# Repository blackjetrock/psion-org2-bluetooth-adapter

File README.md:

# psion-org2-bluetooth-adapter
Bluetooth adapter for Psion Organiser II

NOTE:Very much a prototype that needs modifications to run properly.

An adapter for the Psion Organiser II which has the Comms Link ROM in a Pico. hardware for bluetooth is a WROOM module.
The unit plugs in to the top slot of a PSion Organiser II and allows Bluetooth traffic to be passed on to the organiser.
The original comms link code runs on the Pico as it emulates a datapack ROM.

V1.0
----

Prototype PCB that is not designed to fit in a case.
Power from 1 cell Li-ion. Regulator should take input from jack and drop it to 5V. Battery charger/power path outputs 5.5V down to battery voltage. 
Pico takes output from regulator (5.5V to VBAT) and buck boosts to 3V3. 3V3 output from Pico drives external circuitry up to 300mA.
If running WROOM off 3V3 is too much then use 3V3 regulator off VREG.

V1.1
----

Movd charging circuit to the ETA6002 as soldering the BQxxx was tricky. This circuit doesn't really work as the datasheet has little data so I'm not sure about a lot of aspects of this chip. The code has had to be rewritten to not use interrupts. Instead of using one of the hardware UARTs and a PIO UART the code now uses two UARTS made fom PIOs. This doesn't use interrupts and works a lot better.
Master mode works on th elatest code and I have had two organisers communicating, on ein master mode and pone in slave using the TERM menu. Seems OK. The TRANSMIT menu option messes something up though, although it looks like the data is sent.
Turn off handshaking in the SETUP menu.
9600,n,8,1 is the Psion setting that is needed.

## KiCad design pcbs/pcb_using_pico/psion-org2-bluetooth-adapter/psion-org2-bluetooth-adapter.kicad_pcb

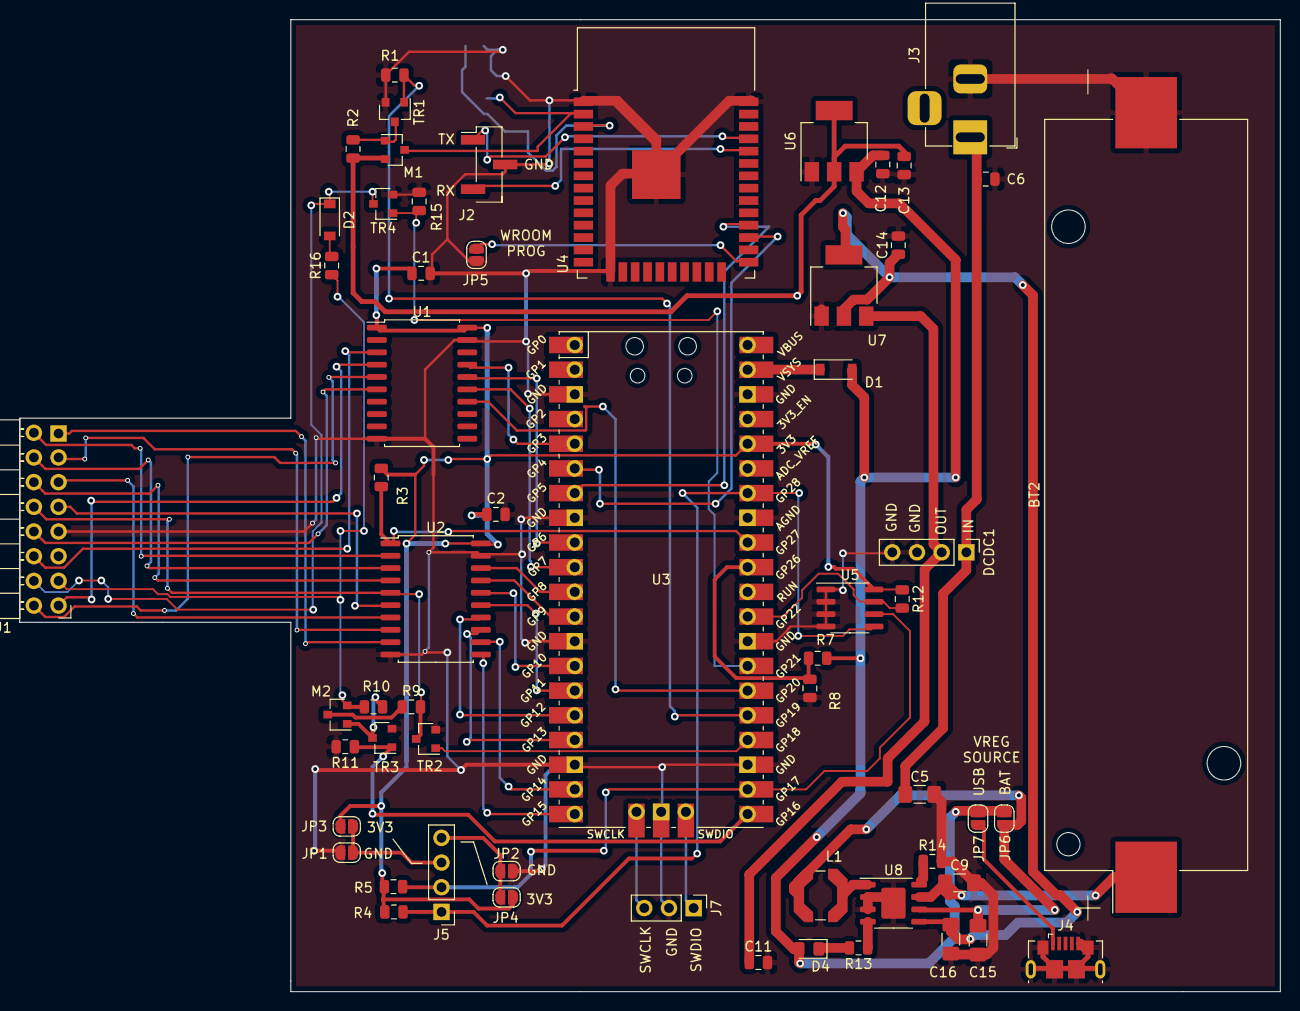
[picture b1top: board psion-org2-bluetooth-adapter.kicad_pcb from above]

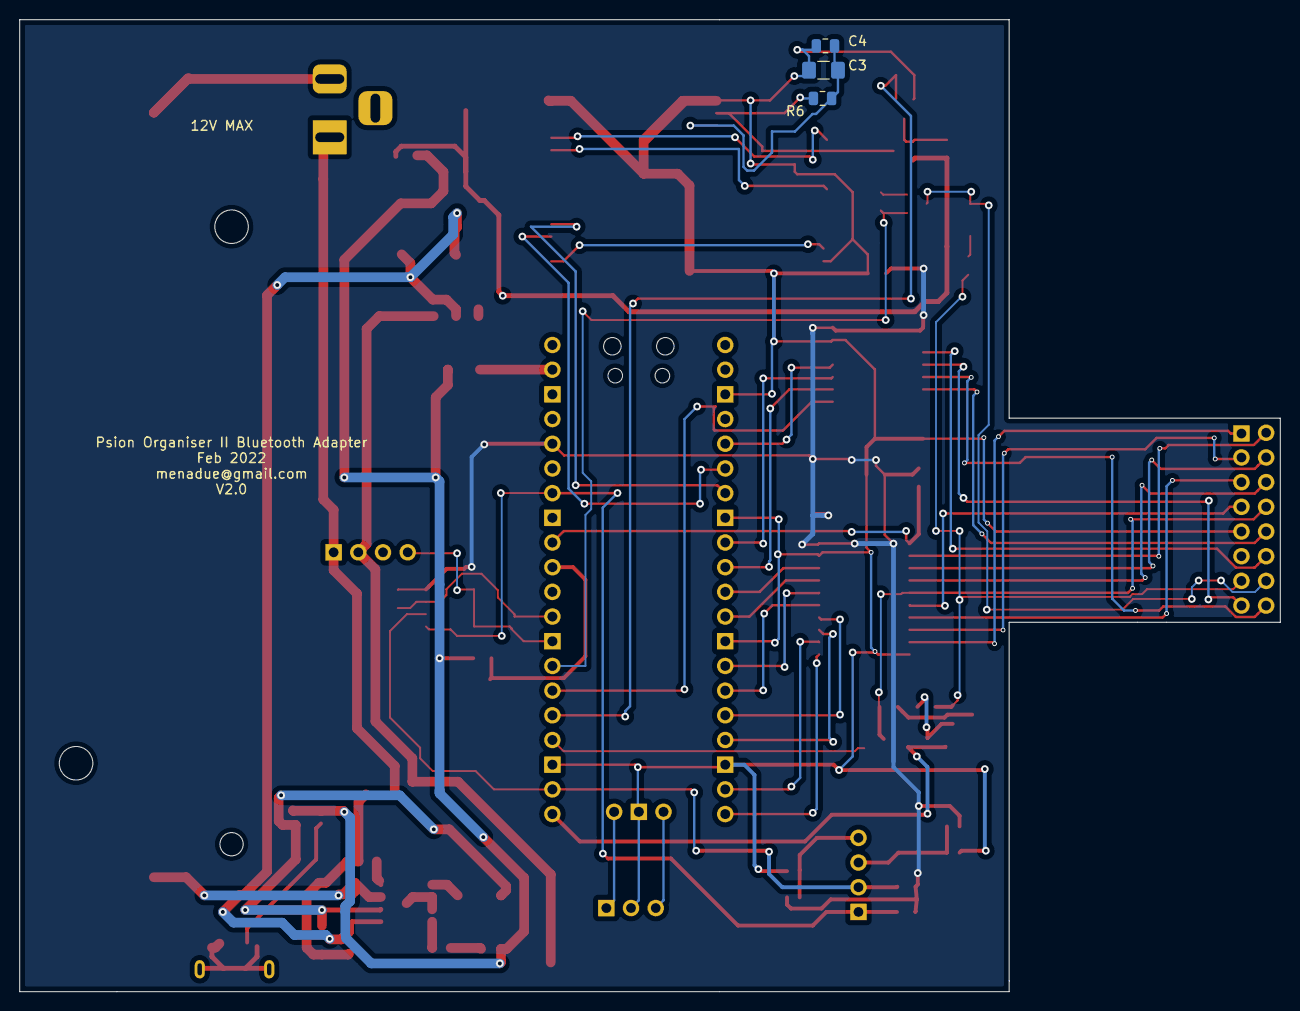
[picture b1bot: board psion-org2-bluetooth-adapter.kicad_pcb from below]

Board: 2 copper layers, 129.7 x 100.0 mm, 62 parts (3 on the bottom side), 65 nets.

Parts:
BT2: Battery_Cell; BatteryHolder_Keystone_1042_1x18650
C1, C2, C4, C6, C11, C12, C13, C14: 100nF; C_0805_2012Metric
C3: 4u7; C_1206_3216Metric_Pad1.42x1.75mm_HandSolder
C5, C16: 10uF; C_1206_3216Metric_Pad1.42x1.75mm_HandSolder
C9: 1uF; C_1206_3216Metric_Pad1.42x1.75mm_HandSolder
C15: 22uF; C_1206_3216Metric_Pad1.42x1.75mm_HandSolder
D1, D2: D_Schottky; D_SOD-123
D4: LED; LED_0805_2012Metric_Pad1.15x1.40mm_HandSolder
DCDC1: dcdc; PinHeader_1x04_P2.54mm_Vertical
J1: Conn_02x08_Odd_Even; Psion_datapak_2x08_P2.54mm_Horizontal
J2: Conn_01x03_Female; PinHeader_1x03_P2.54mm_Vertical_SMD_Pin1Left
J3: Barrel_Jack; BarrelJack_Horizontal
J4: Connector_USB_B_Micro; USB_Micro-B_GCT_USB3076-30-A
J5: Conn_01x04_Female; PinHeader_1x04_P2.54mm_Vertical
J7: Conn_01x03_Female; PinHeader_1x03_P2.54mm_Vertical
JP1, JP2, JP3, JP4, JP5, JP6, JP7: Jumper_NO_Small; SolderJumper-2_P1.3mm_Open_RoundedPad1.0x1.5mm
L1: 2.2uH; L_Coilcraft_LPS5030
M1: P-CHANNEL-MOSFET; SOT-23
M2: Si2301; SOT-23
R1, R2, R3, R6, R7, R8, R9, R12: R_Small; R_0805_2012Metric
R4, R5: 4k7; R_0805_2012Metric
R10, R11: 10k; R_0805_2012Metric
R13: 2k2; R_0805_2012Metric
R14: 500R; R_0805_2012Metric
R15, R16: 47k; R_0805_2012Metric
TR1, TR4: New_Library_Si2302CDS-n-channel; SOT-23
TR2: si2302; SOT-23
TR3: Si2302; SOT-23
U1, U2: 74LS245; SOIC-20W_7.5x12.8mm_P1.27mm
U3: Pico; RPi_Pico_SMD_TH
U4: ESP32-WROOM-32
U5: 24LC32; SOIC-8_3.9x4.9mm_P1.27mm
U6: AMS1117-3.3; SOT-223-3_TabPin2
U7: AMS1117-5.0; SOT-223-3_TabPin2
U8: ETA6002; SOIC-8-1EP_3.9x4.9mm_P1.27mm_EP2.514x3.2mm

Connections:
+3V3: C1.1, C2.1, JP3.2, JP4.2, R3.1, R4.1, R5.1, R12.1, U1.1, U1.20, U2.20, U3.36, U5.8
AC: D2.1, J1.14, TR4.3
AC_ON: R15.2, TR4.1, U3.27
EEPROM_WP: R12.2, U3.29, U5.7
ESP_3V3: C13.1, M1.2, R2.1, U6.2
GND: BT2.2, C1.2, C2.2, C3.2, C4.2, C5.2, C6.2, C9.2, C11.2, C12.2, C13.2, C14.2, C15.2, C16.2, DCDC1.3, DCDC1.4, J1.9, J2.2, J3.2, J4.5, J4.6, J7.2, JP1.2, JP2.2, JP5.2, R1.2, R8.2, R11.2, R14.2, R15.1, TR1.2, TR2.2, TR3.2, TR4.2, U1.10, U1.19, U2.10, U2.19, U3.3, U3.8, U3.13, U3.18, U3.23, U3.28, U3.33, U3.38, U3.42, U4.1, U4.15, U4.38, U4.39, U5.1, U5.2, U5.3, U5.4, U6.1, U7.1, U8.2, U8.3, U8.9
I2C_SCLK: J5.2, R5.2, U3.22, U5.6
I2C_SDA: J5.1, R4.2, U3.34, U5.5
LS_DIR: R3.2, U2.1, U3.32
unnamed: BT2.1, C9.1, U8.6
unnamed: C3.1, C4.1, R6.2, U4.3
unnamed: C5.1, C6.1, DCDC1.1, J3.1
unnamed: C11.1, DCDC1.2, U7.3
unnamed: C14.1, C16.1, U7.2, U8.8
unnamed: C15.1, JP6.2, L1.2, U8.7
unnamed: D1.1, U3.39
unnamed: D2.2, R16.2
unnamed: D4.1, R13.2
unnamed: J2.1, U4.35
unnamed: J2.3, U4.34
unnamed: J4.1, JP7.2
unnamed: J5.3, JP1.1, JP3.1
unnamed: J5.4, JP2.1, JP4.1
unnamed: J7.1, U3.43
unnamed: J7.3, U3.41
unnamed: JP5.1, U4.25
unnamed: L1.1, U8.1
unnamed: M1.1, R2.2, TR1.3
unnamed: M2.1, R10.2, TR3.3
unnamed: M2.3, R9.1
unnamed: R7.2, R8.1, U3.31
unnamed: R13.1, U8.4
unnamed: R14.1, U8.5
PICO_RX: U3.7, U4.28
PICO_TX: U3.6, U4.27
P_SCLK: U1.14, U3.26
P_SD0: U2.18, U3.11
P_SD1: U2.17, U3.12
P_SD2: U2.16, U3.14
P_SD3: U2.15, U3.15
P_SD4: U2.14, U3.16
P_SD5: U2.13, U3.17
P_SD6: U2.12, U3.19
P_SD7: U2.11, U3.20
P_SMR: U1.15, U3.10
P_SOE: U1.16, U3.9
P_SS: U1.17, U3.5
SCLK: J1.10, U1.6
SD0: J1.2, U2.2
SD1: J1.4, U2.3
SD2: J1.6, U2.4
SD3: J1.8, R9.2, TR2.3, U2.5
SD4: J1.7, U2.6
SD5: J1.5, U2.7
SD6: J1.3, U2.8
SD7: J1.1, U2.9
SMR: J1.16, U1.5
SOE: J1.15, U1.4
SS: J1.12, U1.3
TRI_TX: R11.1, TR3.1, U3.21
TX_TO_PSION: TR2.1, U3.24
VCC: J1.13, M2.2, R10.1, R16.1
VCC_ESP: M1.3, R6.1, U4.2
VREG: C12.1, D1.2, D4.2, JP6.1, JP7.1, R7.1, U6.3
WROOM_ON: R1.1, TR1.1, U3.25

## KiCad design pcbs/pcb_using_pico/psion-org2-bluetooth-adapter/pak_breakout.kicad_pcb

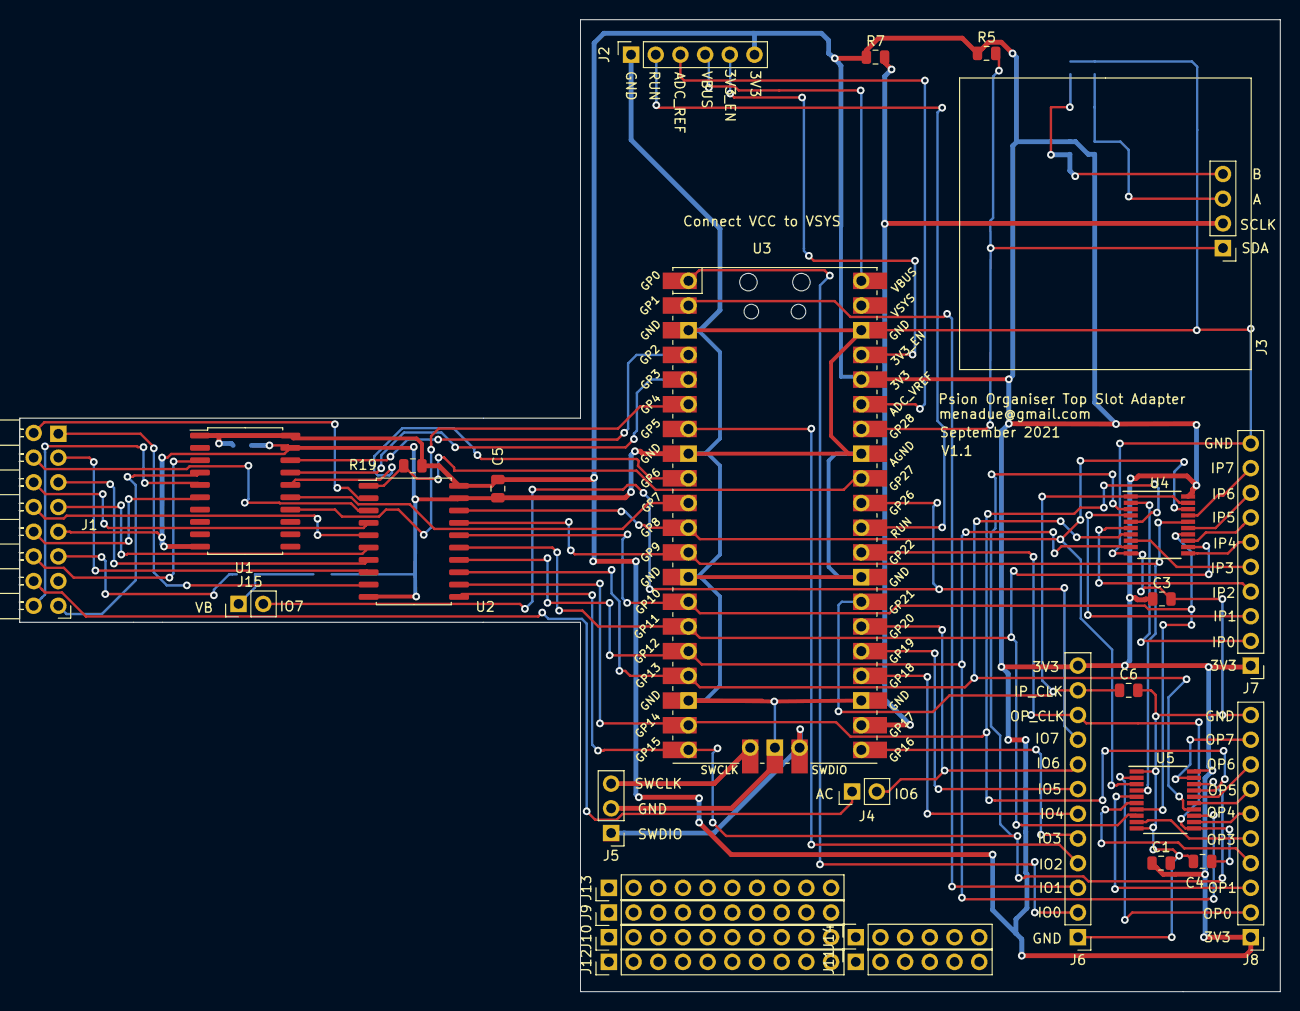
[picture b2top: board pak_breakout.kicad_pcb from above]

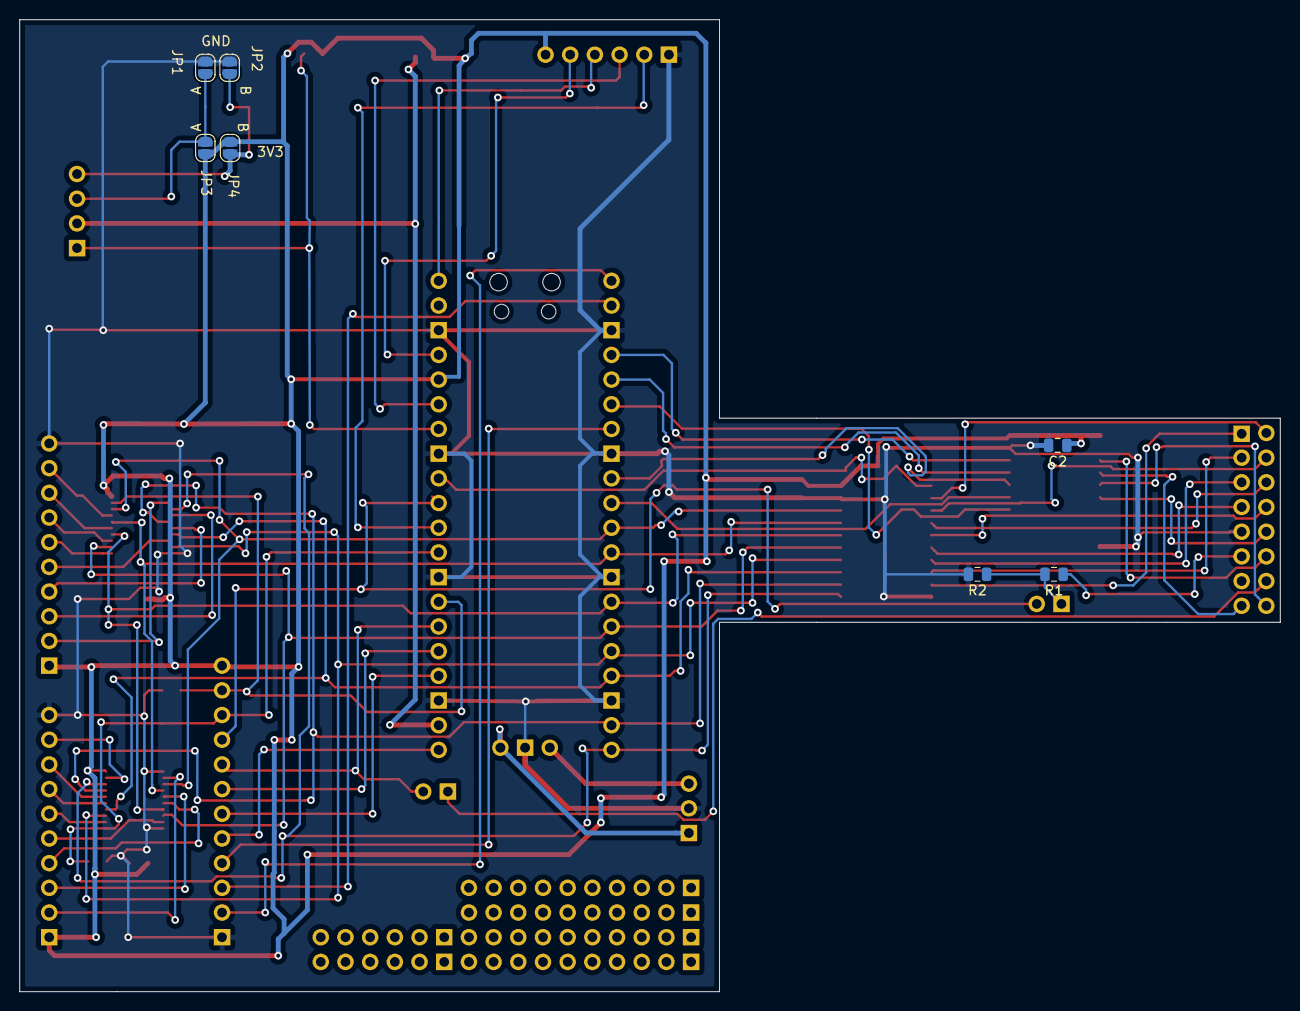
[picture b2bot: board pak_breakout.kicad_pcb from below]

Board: 2 copper layers, 129.7 x 100.0 mm, 35 parts (7 on the bottom side), 67 nets.

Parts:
C1, C3: C_Small; C_0805_2012Metric
C2, C5: 100nF; C_0805_2012Metric
C4, C6: 33pF; C_0805_2012Metric
J1: Conn_02x08_Odd_Even; Psion_datapak_2x08_P2.54mm_Horizontal
J2, J11, J14: Conn_01x06_Female; PinSocket_1x06_P2.54mm_Vertical
J3: Conn_01x04_Female; PinHeader_1x04_P2.54mm_Vertical
J4, J15: Conn_01x02_Male; PinHeader_1x02_P2.54mm_Vertical
J5: Conn_01x03_Female; PinHeader_1x03_P2.54mm_Vertical
J6: Conn_01x12_Female; PinHeader_1x12_P2.54mm_Vertical
J7, J8, J9, J10, J12, J13: Conn_01x10_Female; PinHeader_1x10_P2.54mm_Vertical
JP1, JP2, JP3, JP4: Jumper_NO_Small; SolderJumper-2_P1.3mm_Open_RoundedPad1.0x1.5mm
R1, R2, R19: R_Small; R_0805_2012Metric
R5, R7: 4k7; R_0805_2012Metric
U1, U2: 74LS245; SOIC-20W_7.5x12.8mm_P1.27mm
U3: Pico; RPi_Pico_SMD_TH
U4: 74LS244; TSSOP-20_4.4x6.5mm_P0.65mm
U5: 74LS374; TSSOP-20_4.4x6.5mm_P0.65mm

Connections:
3V3_EN: J2.5, U3.37
+3V3: C1.1, C2.1, C3.1, C5.1, J2.6, J6.12, J7.1, J8.1, JP3.2, JP4.2, R5.1, R7.1, R19.1, U1.1, U1.20, U2.20, U3.36, U4.20, U5.20
AC: J1.14, J4.1
ADC_REF: J2.3, U3.35
GND: C1.2, C2.2, C3.2, C4.2, C5.2, C6.2, J1.9, J2.1, J5.2, J6.1, J7.10, J8.10, JP1.2, JP2.2, R2.2, U1.10, U1.19, U2.10, U2.19, U3.3, U3.8, U3.13, U3.18, U3.23, U3.28, U3.33, U3.38, U3.42, U4.10, U5.1, U5.10
I2C_SCLK: J3.2, R7.2, U3.22
I2C_SDA: J3.1, R5.2, U3.34
IO0: J6.2, U3.1
IO1: J6.3, U3.2
IO2: J6.4, U3.7
IO3: J6.5, U3.21
IO4: J6.6, U3.24
IO5: J6.7, U3.25
IO6: J4.2, J6.8, U3.26
IO7: J6.9, J15.2, U3.31
IP0: J7.2, U4.2
IP1: J7.3, U4.4
IP2: J7.4, U4.6
IP3: J7.5, U4.8
IP4: J7.6, U4.11
IP5: J7.7, U4.13
IP6: J7.8, U4.15
IP7: J7.9, U4.17
IP_CLK: C6.1, J6.11, U3.27, U4.1, U4.19
LS_DIR: R19.2, U2.1, U3.32
unnamed: J3.3, JP1.1, JP3.1
unnamed: J3.4, JP2.1, JP4.1
unnamed: J5.1, U3.43
unnamed: J5.3, U3.41
unnamed: J15.1, R1.2, R2.1
OP0: J8.2, U5.2
OP1: J8.3, U5.5
OP2: J8.4, U5.6
OP3: J8.5, U5.9
OP4: J8.6, U5.12
OP5: J8.7, U5.15
OP6: J8.8, U5.16
OP7: J8.9, U5.19
OP_CLK: C4.1, J6.10, U3.29, U5.11
P_SCLK: U1.14, U3.6
P_SD0: U2.18, U3.11, U4.18, U5.3
P_SD1: U2.17, U3.12, U4.16, U5.4
P_SD2: U2.16, U3.14, U4.14, U5.7
P_SD3: U2.15, U3.15, U4.12, U5.8
P_SD4: U2.14, U3.16, U4.9, U5.13
P_SD5: U2.13, U3.17, U4.7, U5.14
P_SD6: U2.12, U3.19, U4.5, U5.17
P_SD7: U2.11, U3.20, U4.3, U5.18
P_SMR: U1.15, U3.10
P_SOE: U1.16, U3.9
P_SPGM: U1.18, U3.4
P_SS: U1.17, U3.5
RUN: J2.2, U3.30
SCLK: J1.10, U1.6
SD0: J1.2, U2.2
SD1: J1.4, U2.3
SD2: J1.6, U2.4
SD3: J1.8, U2.5
SD4: J1.7, U2.6
SD5: J1.5, U2.7
SD6: J1.3, U2.8
SD7: J1.1, U2.9
SMR: J1.16, U1.5
SOE: J1.15, U1.4
SS: J1.12, U1.3
VB: J1.11, R1.1
VBUS: J2.4, U3.40

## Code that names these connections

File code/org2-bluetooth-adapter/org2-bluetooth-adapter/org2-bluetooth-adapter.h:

// Use this if breakpoints don't work
#define DEBUG_STOP {volatile int x = 1; while(x) {} }

// Are we compiling for the gadget breakout or the picopak?
#define PICOPAK 0

// Bluetooth adapter pinout slightly different
#define BLUETOOTH_ADAPTER             1
#define PSION_XFER                    1    // Compile in Psion serial code
#define TRISTATE_ONLY                 1    // Only drive tristate pin
#define PERMANENT_RX                  1    // RX hardware always running

// Drop into a loop that displays key states and does nothing else
#define KEY_DEBUG_ONLY                0
#define TEST_IOPORT                   0

// Is the monitor present?
#define MONITOR_PRESENT               0
#define MONITOR_ESC_CHAR              '%'

// Interrupts may muck up the pack interface, but it does seem to run with them enabled.
// If USB is ever to work then interrupts need to be enabled.
#define NO_INTERRUPTS_WHILE_POLLING   1
#define TEST_STDIO                    0
#define FORCE_TRISTATE_OFF            0

// Redefine pins to match our hardware
#define PICO_SD_CLK_PIN        5
#define PICO_SD_CMD_PIN       18
#define PICO_SD_DAT0_PIN      19
#define ENABLE_4_PIN           0

#define SUPPORT_ID_BYTE        1
#define PAK_ID_BYTE         0x01
#define READ_ONLY              0
#define INIT_PAK_MEMORY        1
#define FF_FIRST_BYTES         0

// Direct access to GPIO registers is faster, and we need speed
#define DIRECT_GPIO            1

// Number of buttons used for the menu system. The 'exit polling' button is not in this
// list, it is coded as a GPIO line as we don't want to waste time processing the menu
// buttons inthe fast polling loop

#define NUM_BUTTONS            3

// All organiser files are in this subdirectory on the SD card, just to keep things tidy
// and allow the card to be used for other things if needed.
#define PAK_DIR                "/PAK"

// Debounce
#define MAX_BUT_COUNT          6

extern const uint SDA_PIN;
extern const uint SCL_PIN;
extern const int IO0_PIN;
extern const int IO1_PIN;
extern const int IO2_PIN;
extern const int TRISTATE_TX_PIN;
extern const int TX_PSION_PIN;
extern const int WROOM_ON_PIN;
extern const int IO6_PIN;

extern const int OP_CLK_PIN;
extern const int IP_CLK_PIN;

// IO7 can also be used to measure battery voltage
extern const int IO7_PIN;

extern const int SLOT_SPGM_PIN;
extern const int SLOT_SS_PIN;

#if BLUETOOTH_ADAPTER
extern const int SLOT_SCLK_PIN;
#else
extern const int SLOT_SCLK_PIN;
#endif

extern const int SLOT_SOE_PIN;
extern const int SLOT_SMR_PIN;

extern const int SLOT_SD0_PIN;
extern const int SLOT_SD1_PIN;
extern const int SLOT_SD2_PIN;
extern const int SLOT_SD3_PIN;
extern const int SLOT_SD4_PIN;
extern const int SLOT_SD5_PIN;
extern const int SLOT_SD6_PIN;
extern const int SLOT_SD7_PIN;

extern const int LS_DIR_PIN;

#define UART_INTERRUPTS      0     // Interrupt for UART data collection
#define WIFI_UART_PIO        1     // Wifi module UART is PIO based

// Do we use a polling loop of interrupts?
#define USE_INTERRUPTS         0
#define USE_POLLING            1

// For added speed, we poll the address counter stuff on the other core
#define MULTICORE_POLL         1

// Do we drive the OLED?
#define USE_OLED   0

// The address into pak memory
#define PAK_ADDRESS (ss_address | ss_page)

typedef unsigned char BYTE;

// where things are displayed
#define SEL_Y   (2*8)
#define IFN_Y   (1*8)

////////////////////////////////////////////////////////////////////////////////
//
// I2C Port descriptor
//

typedef struct _I2C_PORT_DESC
{
  unsigned char sdaport;
  unsigned char sdabit;
  unsigned char sclport;
  unsigned char sclbit;
} I2C_PORT_DESC;


// Slave device descriptor
typedef struct _I2C_SLAVE_DESC
{
  I2C_PORT_DESC *port;             // Port the device is on
  unsigned char slave_7bit_addr;        // SLave address
} I2C_SLAVE_DESC;

extern I2C_SLAVE_DESC oled0;

////////////////////////////////////////////////////////////////////////////////
//
// PIO UART variables
//

extern PIO wrx_pio;
extern uint wrx_sm;
extern uint wrx_offset;

extern int wrx_init;

// WTX PIO parameters
extern PIO wtx_pio;
extern uint wtx_sm;
extern uint wtx_offset;

extern int wtx_init;

////////////////////////////////////////////////////////////////////////////////
//
// Data received from PIO
#define DATA_RX_LEN 1000

extern int data_rx_in_idx;
extern int data_rx_out_idx;
extern char data_in[DATA_RX_LEN];

// Data sent to Psion
#define DATA_TX_LEN 1000

extern int data_tx_in_idx;
extern int data_tx_out_idx;
extern char data_out[DATA_TX_LEN];

// Wifi module buffers
#define DATA_WRX_LEN 1000

extern int data_wrx_in_idx;
extern int data_wrx_out_idx;
extern char w_data_in[DATA_WRX_LEN];

// Data sent to wifi module

#define DATA_WTX_LEN 1000

extern int data_wtx_in_idx;
extern int data_wtx_out_idx;
extern char w_data_out[DATA_WTX_LEN];

extern int bt_link_up;

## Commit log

2021-12-29 Initial check in
2021-12-30 V1_0 PCB sent off
2022-01-02 Changed circuit to new power arrangement
2022-02-05 Added code
2022-02-08 Can RX from Psion using PIO
2022-02-10 V2.0 PCB, new charger IC, USB power option
2022-02-10 Merged erroneous changes to V1.0 archive started
2022-02-14 V2.0 sent off for fab. New charger IC with more solderable footprint, plus other fixes
2022-02-20 Works with bluetooth serial terminal in both directions
2022-02-21 Removing OLED accesses prevents some errors. RECEIVE and TRANSMIT still give errors
2022-03-05 Updates that stop the code from working. ROm read is problematic, not sure how demo worked.
2022-03-05 Moved wireless work to core1, ROM address handling in core0 loop, works better, maybe
2022-03-11 Updates, psion link not working
2022-03-12 These changes are a bluetooth adapter that doesn't use interrupts as that messes up the ROM load. The PIOs are used for two UARTS and no interrupts and not blocking. Two way comms sems to work The wi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
2022-03-13 Change added that delays RX from Psion until bluetooth is set up. This was causing a lock up when starting the code up. Still gives error on exit from TERM or TRANSMIT. Also gets into a state which s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
2022-03-15 Master mode working now. Still some problems with TRANSMIT menu option. Two way comms between two Psions using TERM menu option works
2022-03-18 Added datasheet for module this may be conneting to
2022-04-12 This is a version of code that works with the BT between a Gemini and the Psion in slave mode. Master mode shouldn't be a problem, but hasn't been tested. This is a base version of code that can be u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
2022-04-17 This code workjs, except for:
    1. Garbage when entering TERM mode appears on the BT device.
    2. Garbage also appears on BT devie before a programmed LPRINT statement.
    3. Garbage appears on a programmed read as well.
    4. Device read error after programmed read.
2022-04-17 Problem with gargabe on BT end when selecting the hardware seems to be fixed. It was due, I think, to the RX line always being active. This meant that transitions were seen when the data bus was bein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
    problems
    We still see DEVICE READ ERROR when running a programmed RX (but not in TERM mode) and
    data is sent to the BT adapter. maybe when more characters
2022-04-17 First version of code that is good enough to be tested with a Total station. The slave code is now set up to look like a Topcon total station. That is for testing with the master code which will look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
